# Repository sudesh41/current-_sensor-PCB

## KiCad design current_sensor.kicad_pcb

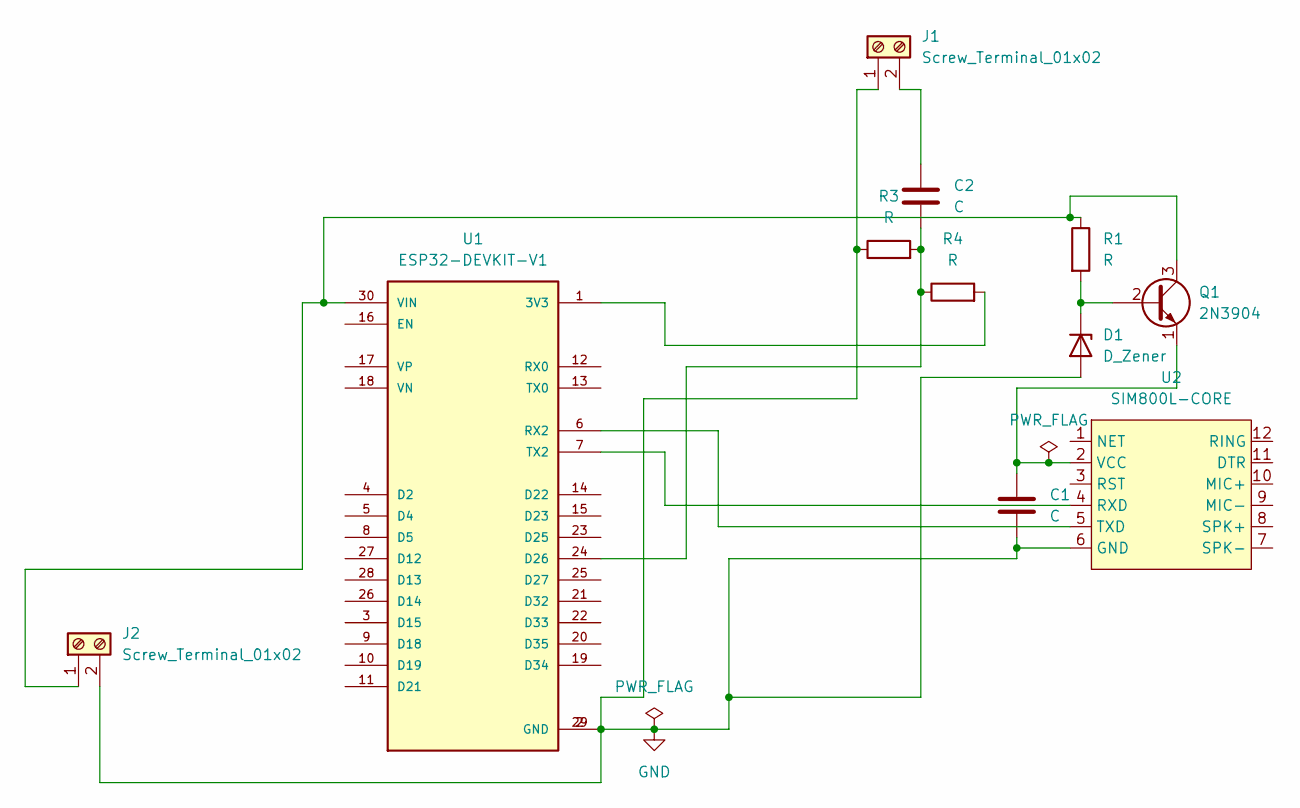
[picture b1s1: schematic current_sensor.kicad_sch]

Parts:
C1, C2: C; C_Radial_D4.0mm_H7.0mm_P1.50mm
D1: D_Zener; D_DO-35_SOD27_P7.62mm_Horizontal
J1, J2: Screw_Terminal_01x02; TerminalBlock_Altech_AK300-2_P5.00mm
Q1: 2N3904; TO-92_Inline
R1, R3, R4: R; R_Axial_DIN0204_L3.6mm_D1.6mm_P7.62mm_Horizontal
U1: ESP32-DEVKIT-V1; MODULE_ESP32_DEVKIT_V1; PARTREV N/A
U2: SIM800L-CORE

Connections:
GND: C1.2, D1.2 (A), J1.1, J2.2, R3.1, U1.2 (GND), U1.29 (GND), U2.6 (GND)
unnamed: D1.1 (K), Q1.2 (B), R1.2
unnamed: C2.1, J1.2
unnamed: J2.1, Q1.3 (C), R1.1, U1.30 (VIN)
unnamed: C1.1, Q1.1 (E), U2.2 (VCC)
unnamed: R4.2, U1.1 (3V3)
unnamed: C2.2, R3.2, R4.1, U1.24 (D26)
unnamed: U1.6 (RX2), U2.5 (TXD)
unnamed: U1.7 (TX2), U2.4 (RXD)

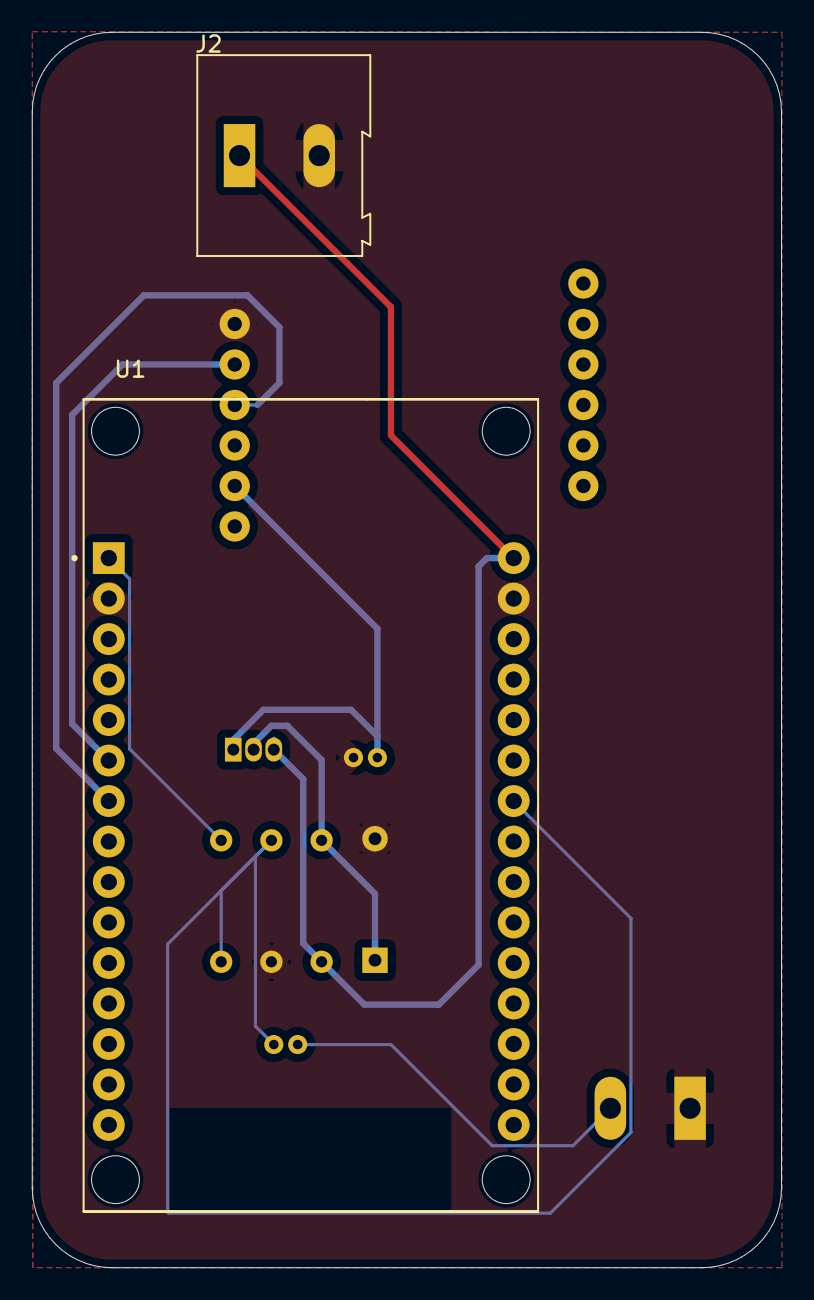
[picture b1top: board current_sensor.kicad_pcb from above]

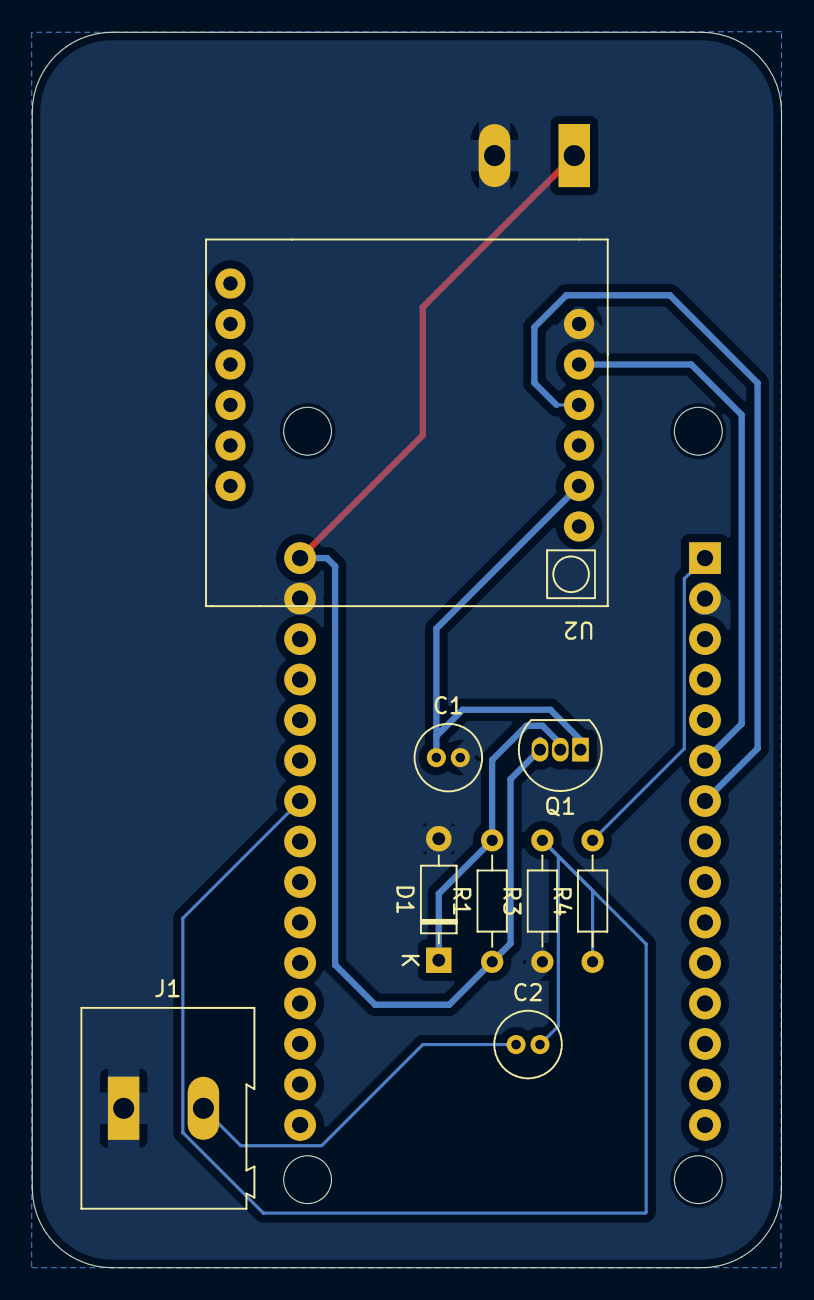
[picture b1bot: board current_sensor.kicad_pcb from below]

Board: 2 copper layers, 47.0 x 77.5 mm, 11 parts (9 on the bottom side), 9 nets.
